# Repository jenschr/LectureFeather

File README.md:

# LectureFeather
A Feather dev board based on ESP32-S3, made for lecturing Embedded Systems (PG5501), M2M (TEK303) and Edge To App (PGR212) at Kristiania University. Feel free to use these Kicad files to make your own boards for use in your own lectures or [purchase premade boards from Maketronics](https://maketronics.no/products/lecturefeather/).

## Thanks to Adafruit
This board is based on the Feather ESP32-S3 from Adafruit and while I have remade the project in Kicad, the job was so much easier thanks to all the great work and research by Adafruit. Thus I'm keeping with the [CC-BY-SA3.0 license](./license.txt) so be sure to share if you redistribute/remake.

This board will make it really easy for my students to extend the base functionality using FeatherWings and Stemma sensors from Adafruit. I highly recommend Adafruit products and they do fantastic work for the hardware commmunity.

## Usage
To use the board, set the Arduino IDE, PlatformIO or another IDE to use the board named "Adafruit ESP32-S3 Feather". This will ensure proper operation so that defines such as LED_BUILTIN and auto-programming will work. Refer to the original [Adafruit Guide](https://learn.adafruit.com/adafruit-esp32-s2-feather) for details.

As in the Adafruit design, special features are on these pins:
* I2C is on IO03 and IO04. Initiate I2C using wire.begin(3,4);
* Separate power supply for I2C devices are on IO07. Set this low before going into low power mode.
* LED_BUILTIN is on IO13

Here are some differences from the Adafruit development board:

* Light/lux sensor (LTR-329) on I2C address 0x29
* Temperature/moisture sensor (SHT31) on I2C address 0x44
* Accelerometer (LIS3DH) on I2C address 0x18
* The Hall sensor (MT8691AT) is on IO01. Larger ESP modules have this builtin, but the Mini modules do not, so I added this.
* I've also swapped the Neopixel (ws2812-type) to a Dotstar (APA102-2020). This is using IO33 for data and IO21 for clock.
* I've removed the LC709203 battery monitor as that wasn't available for months and I could not easily find a good alternative.

## Project files

## Known issues
- Version 1.0 had the Temperature sensor placed too close to the ESP32 module. This caused Temperature readins to be off by quite a bit. For Version 1.1 the sensor was moved further away, but it's still reading too high. Next version should move it all the way back to the USB connector as well as add cutouts to reduce coupling to the copper planes on the PCB.
- The board is pin compatible with both S2 and S3 MINI modules. The choice of using S3 modules in 2023 is the one I've regretted the most since tooling just isn't there for the alternate USB mode. This requires lots of custom setup to work well. I made a [writeup on solving the ESP32-S3 issues for PlatformIO](https://flashgamer.com/blog/comments/solving-platformio-issues-with-the-adafruit-feather-s3), but there are issues for Arduino as well. I've tried solving some of these with the tooling, but I'm having a hard time explaining to the maintainers what is S3 issues vs my custom board. They seem to (rightfully) think that anyone commenting on a board programming issue don't know what they're talking about, so this may take time. Use the S2 for less tooling problems is my current suggestion.
- I'm thinking on adding one more sensor in the next version of the board. I'm open to suggestions on what to add, so find my email on my blog and message me.

### PCB
The [PCB folder](./pcb) holds all the Kicad files I've used for making my boards. Please do not include any logos if you remake this board. Here you'll also find the Errata for versions of this board.

### Code
The [Example folder](./examples) holds a single .ino file that will test all the features of the board. Lots of libraries are required, so be sure to read the Include section of the file. Project file for PlatformIO used for default firmware [can be found here](https://github.com/jenschr/TestAll).

Please note that to make ESP32-S3 work painless in PlatformIO [ref](https://github.com/espressif/arduino-esp32/issues/6762#issuecomment-1182821492), we need to add the following two lines to platformio.ini:

    monitor_speed = 115200
    build_flags =   -DARDUINO_USB_MODE=1
                    -DARDUINO_USB_CDC_ON_BOOT=1
    
Note that if you use PlatformIO, I wrote up a [long article on how to solve the most common issues with the ESP32-S3 for PlatformIO on my blog](https://flashgamer.com/blog/comments/solving-platformio-issues-with-the-adafruit-feather-s3).

### BOM
The [HTML BOM](./bom) lists all the components used in the design and shows their position on the board. Great for curious students that want to know it all.

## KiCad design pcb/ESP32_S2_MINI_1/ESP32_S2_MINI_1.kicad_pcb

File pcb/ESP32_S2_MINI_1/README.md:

# Dev board for lecturing Embedded & M2M

## Errata
Known bugs and limitations for this project

### Version 1.1
Yet to be produced & tested.

### Version 1.0
- APA102 used IO26 for data. This conflicts with PSRAM. Move to IO33.
- Temperature sensor is placed too close the the ESP-module, so it reads the temp of the board, not the air around it. Adafruit has a [similar problem](https://learn.adafruit.com/adafruit-esp32-s2-feather/pinouts#bme280-temperature-humidity-and-pressure-sensor-3106370) with the BME280 they use in their design.
- Type-C receptacle footprint works great for industrial production, but gives 30% failure/bridges when producing locally. Reduce size of pads for next revision.
- Boot-button needs more space so it's easier to press

### Version 0.9 (not published to git)
- Swapped battery pins
- Swapped unstable BH1730 sensor

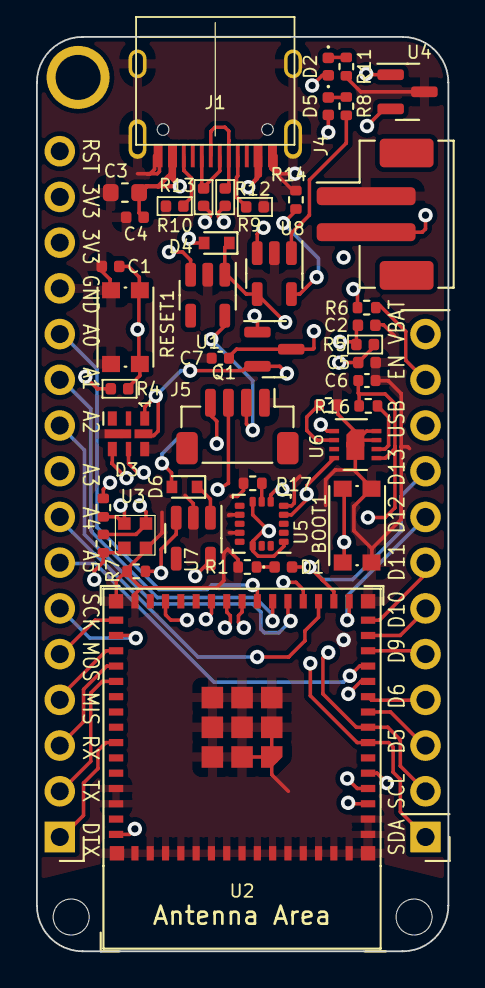
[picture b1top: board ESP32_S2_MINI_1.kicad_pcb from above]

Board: 4 copper layers, 22.9 x 50.8 mm, 50 parts (1 on the bottom side), 49 nets.

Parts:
BOOT1: BOOT; SW_Push_1P1T_NO_CK_KMR2
C1, C2, C4, C5, C6, C7: 0.1uF; C_0402_1005Metric
C3: 10uF; C_0603_1608Metric
D1, D2, D5: LED; LED_0402_1005Metric
D3: APA102-2020; LED-APA102-2020
D4, D6: MSK4005; D_SOD-523
H1: MountingHole; MountingHole_2.5mm_Pad
H2, H3: MountingHole; MountingHole_2.0mm_NoPad
H4: HK Logo; HK_engelsk-logo
J1: USB_C_Receptacle_USB2.0; TYPE-C-31-M-12
J2: Conn_01x12_Female; PinHeader_1x12_P2.54mm_Vertical
J3: Conn_01x16_Female; PinHeader_1x16_P2.54mm_Vertical
J4: Conn_01x02_Female; JST_PH_B2B-PH-SM4-TB_1x02-1MP_P2.00mm_Vertical
J5: STEMMA; JST_SH_BM04B-SRSS-TB_1x04-1MP_P1.00mm_Vertical
Q1: DMG3415u; SOT-23
R1, R8, R11: 1k; R_0402_1005Metric
R2, R3, R4, R5, R15, R16, R17: 10k; R_0402_1005Metric
R6, R7: 100k; R_0402_1005Metric
R9, R10, R14: 5.1k; R_0402_1005Metric
R12, R13: 33R; R_0402_1005Metric
RESET1: RESET; SW_Push_1P1T_NO_CK_KMR2
U1, U7: AP2112K-3.3; SOT-23-5
U2: ESP32-S3-MINI-1; ESP32-S2-MINI-1
U3: LTR-329ALS-01
U4: MT8691AT; SOT-23
U5: LIS3DH; LGA-16_3x3mm_P0.5mm_LayoutBorder3x5y
U6: SHT31-DIS; Sensirion_DFN-8-1EP_2.5x2.5mm_P0.5mm_EP1.1x1.7mm
U8: MCP73831-2-OT; SOT-23-5

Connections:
+3.3VA: C6.1, R2.2, R3.2, R16.1, U3.1 (VDD), U5.1 (VDD_IO), U5.8 (CS), U5.14 (VDD), U6.5 (VDD), U7.5 (VOUT)
+3V3: C5.1, D2.2 (A), J3.14, J3.15, J5.2, R4.2, R5.2, U1.5 (VOUT), U2.3 (3V3), U4.1 (VCC)
/APA_CLOCK: D3.5 (CKI), U2.25 (GPIO21)
/APA_DATA: D3.4 (SDI), U2.28 (GPIO33)
/BOOT: BOOT1.1, C2.1, R5.1, U2.4 (GPIO0/BOOT)
/DN: J1.A7 (D-), J1.B7 (D-), R12.1
/DP: J1.A6 (D+), J1.B6 (D+), R13.1
/ENABLE: C1.1, R4.1, RESET1.1, U2.45 (CHIP/PU/RESET)
/USB_DN: R12.2, U2.23 (USB_D-/ADC2_CH8/GPIO19)
/USB_DP: R13.2, U2.24 (USB_D+/ADC2_CH9/GPIO20)
/VB: D3.1 (VDD), D4.1 (K), D5.2 (A), Q1.2 (S), R6.2, U1.1 (VIN), U8.4 (VDD)
A0: J3.12, U2.22 (ADC2_CH6/DAC_1/GPIO18)
A1: J3.11, U2.21 (ADC2_CH7/DAC_2/GPIO17)
A2: J3.10, U2.20 (GPIO16/ADC2_CH5/XTAL_32K_N)
A3: J3.9, U2.19 (GPIO15/ADC2_CH4/XTAL_32K_P)
A4: J3.8, U2.18 (GPIO14/ADC2_CH3)
A5: J3.7, U2.12 (GPIO8/ADC1_CH7)
D5: J2.3, U2.9 (GPIO5/ADC1_CH4)
D6: J2.4, U2.10 (GPIO6/ADC1_CH5)
D9: J2.5, U2.13 (GPIO9/ADC1_CH8)
D10: J2.6, U2.14 (GPIO10/ADC1_CH9)
D11: J2.7, U2.15 (GPIO11/ADC2_CH0)
D12: J2.8, U2.16 (GPIO12/ADC2_CH1)
D13: D1.2 (A), J2.9, U2.17 (GPIO13/ADC2_CH2)
DEBUG_TX: J3.1, U2.39 (GPIO43/U0TXD/PROG)
EN: J2.11, R6.1, U1.3 (EN)
GND: BOOT1.2, C1.2, C2.2, C3.2, C4.2, C5.2, C6.2, C7.2, D3.6 (GND), J1.A1 (GND), J1.A12 (GND), J1.B1 (GND), J1.B12 (GND), J1.S1 (SHIELD), J3.13, J4.1, J5.1, R1.1, R7.1, R9.2, R10.2, R11.1, R14.1, R15.1, R17.1, RESET1.2, U1.2 (GND), U2.1 (GND), U2.2 (GND), U2.30 (GND), U2.42 (GND), U2.43 (GND), U2.46 (GND), U3.2 (GND), U4.3 (GND), U5.5 (GND), U5.10 (GND), U5.12 (GND), U6.7 (R), U6.8 (VSS), U6.9 (VSS), U7.2 (GND), U8.2 (VSS)
I2C_PWR: R7.2, U2.11 (GPIO7/ADC1_CH6), U7.3 (EN)
I2C_SCL: J2.2, J5.4, R2.1, U2.8 (GPIO4/ADC1_CH3), U3.4 (SCL), U5.4 (SCL/SPC), U6.4 (SCL)
I2C_SDA: J2.1, J5.3, R3.1, U2.7 (GPIO3/ADC1_CH2), U3.3 (SDA), U5.6 (SDA/SDI/SDO), U6.1 (SDA)
MAG: U2.5 (GPIO1/ADC1_CH0), U4.2 (OUTPUT)
MISO: J3.4, U2.33 (GPIO37)
MOSI: J3.5, U2.31 (GPIO35)
unnamed: D1.1 (K), R1.2
unnamed: D2.1 (K), R11.2
unnamed: D5.1 (K), R8.2
unnamed: D6.1 (K), U7.1 (VIN)
unnamed: J1.A5 (CC1), R9.1
unnamed: J1.B5 (CC2), R10.1
unnamed: R8.1, U8.1 (STAT)
unnamed: R14.2, U8.5 (PROG)
unnamed: R15.2, U6.2 (ADDR)
unnamed: R16.2, U6.6 (~RESET)
unnamed: R17.2, U5.7 (SDO/SA0)
RX: J3.3, U2.34 (GPIO38)
SCK: J3.6, U2.32 (GPIO36)
TX: J3.2, U2.35 (MTCK/JTAG/GPIO39)
USB: C3.1, C4.1, D4.2 (A), D6.2 (A), J1.A4 (VBUS), J1.A9 (VBUS), J1.B4 (VBUS), J1.B9 (VBUS), J2.10, Q1.1 (G)
VBAT: C7.1, J2.12, J4.2, Q1.3 (D), U8.3 (VBAT)

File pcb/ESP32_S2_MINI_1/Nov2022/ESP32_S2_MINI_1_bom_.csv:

Component,Description,Part,References,Value,Footprint,Quantity Per PCB,Datasheet,MFGR,MPN
1,"Push button switch, generic, two pins",SW_Push,BOOT1,BOOT,SW_Push_1P1T_NO_CK_KMR2,1,,C&K,KMR241GLFS
2,Unpolarized capacitor,C,C1 C2 C4 C5 C6 C7,0.1uF,C_0402_1005Metric,6,~,Samsung,CL10B104KO8NFNC
3,"Unpolarized capacitor, small symbol",C_Small,C3,10uF,C_0603_1608Metric,1,~,,
4,RGB LED with integrated controller,APA102-2020,D3,APA102-2020,LED-APA102-2020,1,http://www.led-color.com/upload/202210/LC8822-2020-6%20EN.pdf,"Shenzhen LED Color Co.,LTD",LC8822-2020-6
5,Light emitting diode,LED,D1 D2 D5,LED,LED_0402_1005Metric,3,~,,
6,Diode,D,D4 D6,MSK4005,D_SOD-523,2,~,Shikues,MSK4005
7,"Generic connector, single row, 01x02, script generated (kicad-library-utils/schlib/autogen/connector/)",Conn_01x02_Female,J4,Conn_01x02_Female,JST_PH_B2B-PH-SM4-TB_1x02-1MP_P2.00mm_Vertical,1,~,,
8,"Generic connector, single row, 01x12, script generated (kicad-library-utils/schlib/autogen/connector/)",Conn_01x12_Female,J2,Conn_01x12_Female,PinHeader_1x12_P2.54mm_Vertical,1,~,,
9,"Generic connector, single row, 01x16, script generated (kicad-library-utils/schlib/autogen/connector/)",Conn_01x16_Female,J3,Conn_01x16_Female,PinHeader_1x16_P2.54mm_Vertical,1,~,,
10,"Generic connector, single row, 01x04, script generated (kicad-library-utils/schlib/autogen/connector/)",Conn_01x04_Female,J5,STEMMA,JST_SH_BM04B-SRSS-TB_1x04-1MP_P1.00mm_Vertical,1,~,,
11,USB 2.0-only Type-C Receptacle connector,USB_C_Receptacle_USB2.0,J1,USB_C_Receptacle_USB2.0,TYPE-C-31-M-12,1,https://www.usb.org/sites/default/files/documents/usb_type-c.zip,Korean Hroparts Elec,TYPE-C-31-M-12
12,"-3A Id, -20V Vds, P-Channel MOSFET, SOT-23",DMG2301L,Q1,DMG3415u,SOT-23,1,https://www.diodes.com/assets/Datasheets/DMG2301L.pdf,Diodes Incorporated,DMG3415U-7
13,Resistor,R,R12 R13,33R,R_0402_1005Metric,2,~,,
14,Resistor,R,R1 R8 R11,1k,R_0402_1005Metric,3,~,,
15,Resistor,R,R9 R10 R14,5.1k,R_0402_1005Metric,3,~,,
16,Resistor,R,R2 R3 R4 R5 R15 R16 R17,10k,R_0402_1005Metric,7,~,Stackpole,RMCF0603JG10K0
17,Resistor,R,R6 R7,100k,R_0402_1005Metric,2,~,,
18,"Push button switch, generic, two pins",SW_Push,RESET1,RESET,SW_Push_1P1T_NO_CK_KMR2,1,,C&K,KMR241GLFS
19,"600mA low dropout linear regulator, with enable pin, 3.8V-6V input voltage range, 3.3V fixed positive output, SOT-23-5",AP2112K-3.3,U1 U7,AP2112K-3.3,SOT-23-5,2,https://www.diodes.com/assets/Datasheets/AP2112.pdf,Diodes Incorporated,AP2112K-3.3TRG1
20,"ESP32-S2-MINI-1 and ESP32-S2-MINI-1U are two powerful, generic Wi-Fi MCU modules that have a rich set of peripherals. They are an ideal choice for a wide variety of application scenarios relating to Internet of Things (IoT), wearable electronics and smart home.",ESP32-S2-MINI-1,U2,ESP32-S3-MINI-1,ESP32-S2-MINI-1,1,https://www.espressif.com/sites/default/files/documentation/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,Espressif Systems,ESP32-S3-MINI-1-N8
21,"3-Axis Accelerometer, 2/4/8/16g range, I2C/SPI interface, LGA-16",LIS3DH,U5,LIS3DH,LGA-16_3x3mm_P0.5mm_LayoutBorder3x5y,1,https://www.st.com/resource/en/datasheet/cd00274221.pdf,ST,LIS3DH
22,"ambient light sensor, i2c interface, 0.01 to 64k lux, 2.4-3.6V",LTR-329ALS-01,U3,LTR-329ALS-01,LTR-329ALS-01,1,https://no.mouser.com/datasheet/2/239/liteon_LTR-329ALS-01-1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,Lite-On,LTR-329ALS-01
23,"Single cell, Li-Ion/Li-Po charge management controller, 4.20V, Tri-State Status Output, in SOT23-5 package",MCP73831-2-OT,U8,MCP73831-2-OT,SOT-23-5,1,http://ww1.microchip.com/downloads/en/DeviceDoc/20001984g.pdf,Microchip Technology,MCP73831T-4ADI/OT
24,"Hall Effect Switch, SOT-23",SM351LT,U4,MT8691AT,SOT-23,1,https://sensing.honeywell.com/honeywell-sensing-nanopower-se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,Honeywell,MT8691AT
25,"I²C humidity and temperature sensor, ±2%RH, ±0.2°C, DFN-8",SHT31-DIS,U6,SHT31-DIS,Sensirion_DFN-8-1EP_2.5x2.5mm_P0.5mm_EP1.1x1.7mm,1,https://www.sensirion.com/fileadmin/user_upload/customers/se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,Sensiron,SHT31-DIS





Component Groups:,25
Component Count:,46
Fitted Components:,46
Number of PCBs:,1
Total components:,46
Schematic Version:,
Schematic Date:,
PCB Variant:,default
BoM Date:,"2022 November 23, Wednesday 21:07:22"
Schematic Source:,ESP32_S2_MINI_1.kicad_sch
KiCad Version:,Eeschema (6.0.4-0)

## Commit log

2022-09-15 First public version
2022-09-22 Version 1.1, see Errata for fixes
2022-09-22 typo
2022-11-16 Updated pin number for v1.2 of the board
2022-11-16 Improved error output
2023-01-09 S3 Compatibility
2023-01-11 S3 version
2023-05-26 Update README.md
    added known issues
2025-02-16 Added text to show it's now available for purchase also
